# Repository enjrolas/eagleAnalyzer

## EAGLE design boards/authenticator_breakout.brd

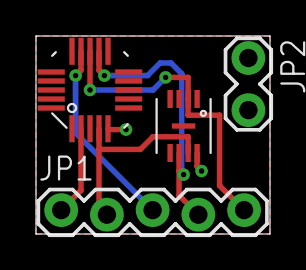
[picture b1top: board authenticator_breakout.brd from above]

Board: 2 copper layers, 13.0 x 11.0 mm, 4 parts (0 on the bottom side), 7 nets.

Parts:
JP1: 1X05_LOCK
JP2: 1X02_LOCK
U$2: AUTHENTICATORQFN; AUTH_QFN20
U$4: AUTHENTICATOR_2C; AUTH_SQC

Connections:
!AUTH_RESET: JP1.2, U$2.P$4, U$4.P$7
+3V3: JP2.2, U$2.P$5, U$4.P$8
GND: JP2.1, U$2.P$11, U$4.P$1
MODE0: JP1.3, U$2.P$14
MODE1: JP1.1, U$2.P$2
SCL: JP1.4, U$2.P$12, U$4.P$6
SDA: JP1.5, U$2.P$13, U$4.P$2

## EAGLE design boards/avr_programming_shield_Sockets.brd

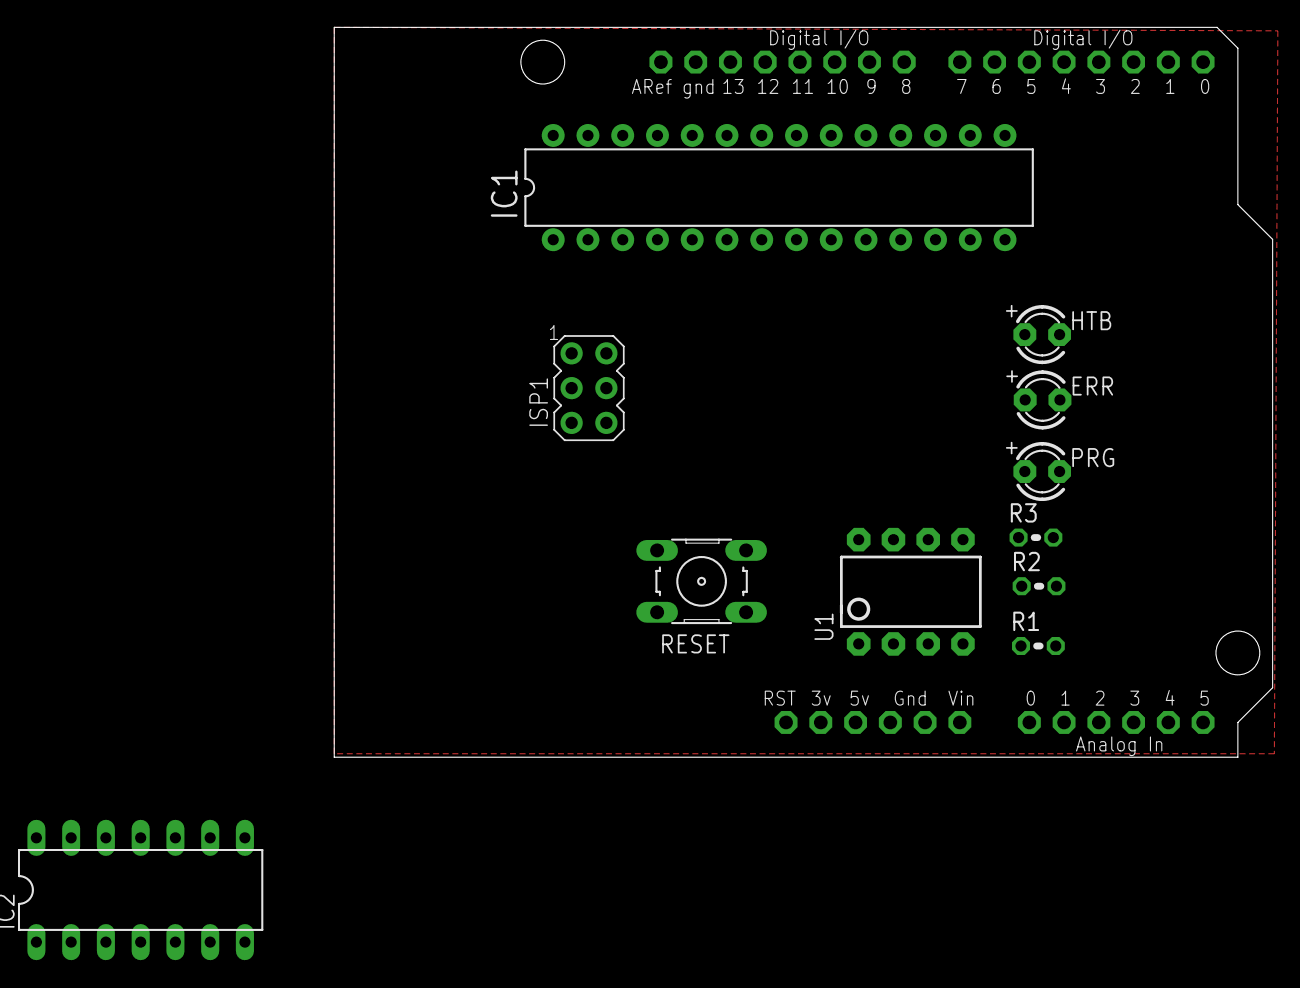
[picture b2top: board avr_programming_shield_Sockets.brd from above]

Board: 2 copper layers, 68.6 x 53.3 mm, 13 parts (0 on the bottom side), 13 nets, no tracks yet.

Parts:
E$1: OSHWLOGO_TOL_0.2
ERR: LED3MM
HTB: LED3MM
IC1: ATMEGA168PROUND; DIL28-3-ROUND
IC2: TINY24/44/84-PU; DIL14
ISP1: AVRISP-6; AVRISP
PRG: LED3MM
R1, R2, R3: 0204V
RESET: B3F-10XX
U1: TINY85-20-DIP; DIP08
U$1: ARDUINO-NOHOLE

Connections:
GND: IC1.8, IC1.22, IC2.14, ISP1.6, R1.1, R2.1, R3.1, RESET.1, RESET.2, U1.4, U$1.GND, U$1.GND1, U$1.GND2
unnamed: IC1.19, ISP1.3, U1.7, U$1.D13
unnamed: IC1.18, ISP1.1, U1.6, U$1.D12
unnamed: IC1.1, ISP1.5, U1.1, U$1.D10
unnamed: IC1.17, ISP1.4, U1.5, U$1.D11
unnamed: PRG.K, R1.2
unnamed: ERR.K, R2.2
unnamed: HTB.K, R3.2
unnamed: IC1.13, PRG.A
unnamed: ERR.A, IC1.14
unnamed: HTB.A, IC1.15
RESET: RESET.3, RESET.4, U$1.RESET
VCC: IC1.7, IC1.20, IC1.21, IC2.1, ISP1.2, U1.8, U$1.5V

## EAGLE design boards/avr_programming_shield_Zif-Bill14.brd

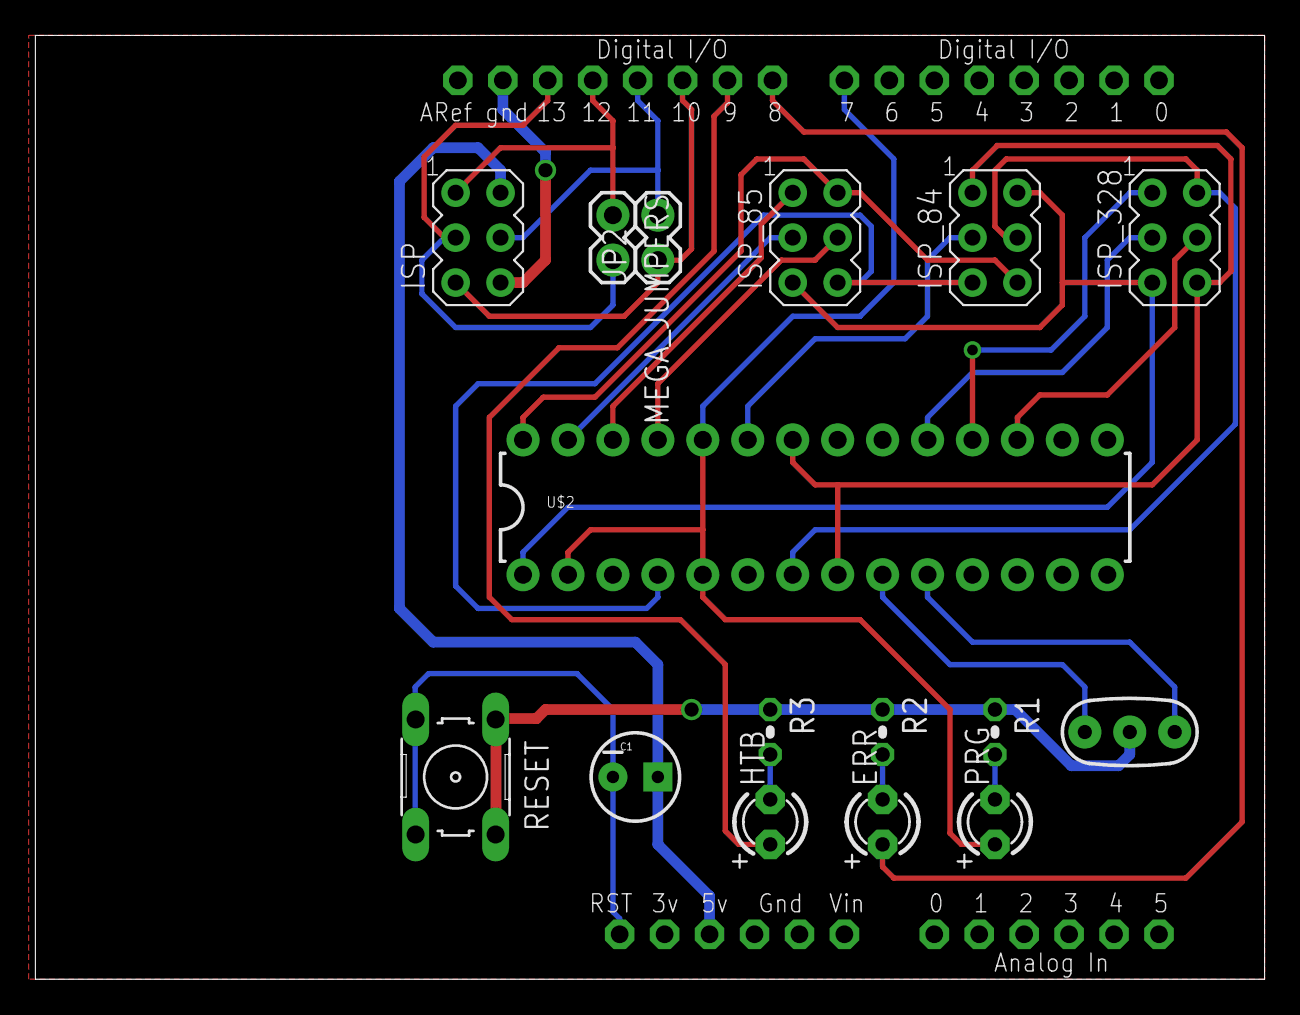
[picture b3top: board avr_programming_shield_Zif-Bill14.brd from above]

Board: 2 copper layers, 69.5 x 53.3 mm, 18 parts (0 on the bottom side), 27 nets.

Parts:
16MHZ: RESONATORPTH; RESONATOR-PTH
C1: 10uF; CPOL-RADIAL-10UF-25V
E$1: OSHWLOGO_TOL_0.2
ERR: LED3MM
HTB: LED3MM
ISP: AVRISP-6; AVRISP
ISP_84, ISP_85, ISP_328: AVRISP-6; AVRISP
JP2: 1X02
MEGA_JUMPERS: 1X02
PRG: LED3MM
R1, R2, R3: 0204V
RESET: B3F-10XX
U$1: ARDUINO-NOHOLE
U$2: ZIFSOCKET-28-3ZIFFSOCKET-28-3; DIL28-3-ZIF_SOCKET

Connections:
COMMON_D3: PRG.A, U$1.D7, U$2.2, U$2.5, U$2.24
GND: 16MHZ.2, ISP.6, R1.1, R2.1, R3.1, RESET.1, RESET.2, U$1.GND, U$1.GND1, U$1.GND2
unnamed: ISP_328.4, U$2.17
unnamed: ISP.3, MEGA_JUMPERS.2, U$1.D13
unnamed: ISP.1, MEGA_JUMPERS.1, U$1.D12
unnamed: ISP_328.1, U$2.18
unnamed: ISP.5, JP2.1, U$1.D10
unnamed: ISP_328.3, U$2.19
unnamed: PRG.K, R1.2
unnamed: ERR.K, R2.2
unnamed: HTB.K, R3.2
unnamed: ISP_84.4, ISP_328.2, U$2.7
unnamed: ISP.4, JP2.2, U$1.D11
unnamed: ISP_84.2, ISP_85.5, ISP_328.5, U$2.1
unnamed: ISP_84.3, U$2.23
unnamed: ISP_84.6, ISP_85.2, U$2.28
unnamed: HTB.A, U$1.D9
unnamed: ISP_84.5, ISP_85.6, U$2.4
unnamed: ISP_85.4, U$2.25
unnamed: ISP_85.1, U$2.26
unnamed: ISP_85.3, U$2.27
unnamed: 16MHZ.1, U$2.9
unnamed: ERR.A, U$1.D8
unnamed: 16MHZ.3, U$2.10
unnamed: ISP_84.1, ISP_328.6, U$2.8, U$2.22
RESET: C1.2, RESET.3, RESET.4, U$1.RESET
VCC: C1.1, ISP.2, U$1.5V

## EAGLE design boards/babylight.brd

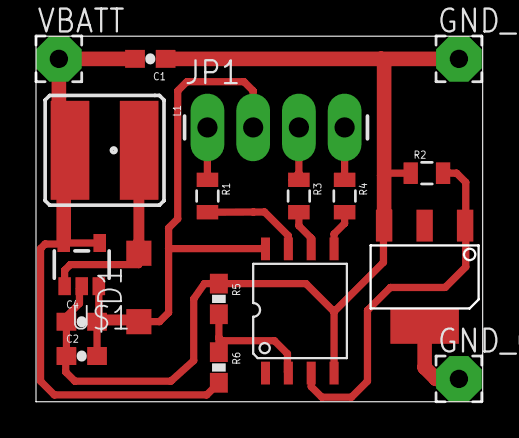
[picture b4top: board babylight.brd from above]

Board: 2 copper layers, 24.8 x 20.3 mm, 18 parts (0 on the bottom side), 13 nets.

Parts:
C1, C2: 22uF; 0603-CAP
C4: 1uF; 0603-CAP
D1: MBR0520; SOD123
GND_IN: 2,54/1,0
GND_OUT: 2,54/1,0
JP1: 1X04_LONGPADS
L1: 22uH; CR54
R1: 560; 0805
R2: 100K; 0805
R3, R4: 270; 0805
R5: 150K; 0603-RES
R6: 68K; 0603-RES
U$1: SP6641A; SOT23-5
U$2: ATTINY13; WSOIC-8
U$7: FQT13N06LTF; SOT-223
VBATT: 2,54/1,0

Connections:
5V: C2.2, C4.2, D1.C, JP1.2, U$1.3, U$2.8
BLU: JP1.4, R4.1
GND: C1.1, C2.1, C4.1, GND_IN.1, R2.1, R5.1, U$1.2, U$2.4, U$7.3
GND_OUT: GND_OUT.1, U$7.4
GRN: JP1.3, R3.1
unnamed: R5.2, R6.1, U$2.2
unnamed: D1.A, L1.P$1, U$1.1
unnamed: R4.2, U$2.5
unnamed: R3.2, U$2.6
unnamed: R1.2, U$2.7
RED: JP1.1, R1.1
SW: R2.2, U$2.3, U$7.1
VBATT: C1.2, L1.P$2, R6.2, U$1.4, U$1.5, VBATT.1

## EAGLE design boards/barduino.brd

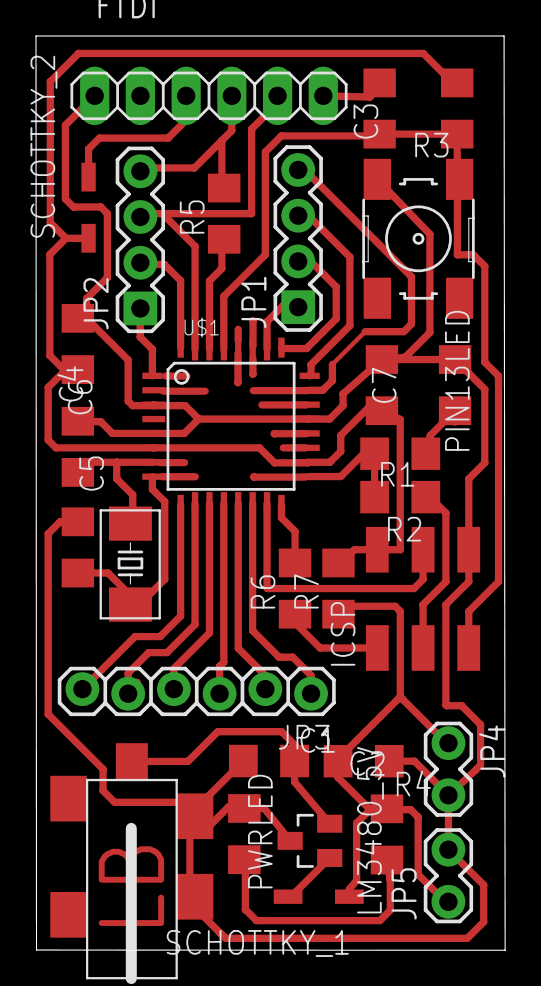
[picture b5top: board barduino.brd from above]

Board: 2 copper layers, 26.1 x 50.8 mm, 30 parts (0 on the bottom side), 28 nets.

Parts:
C1, C2: 10uF; 1206
C3, C6, C7: .1uF; 1206
C4, C5: 18pF; 1206
FTDI: 1X06
ICSP: 2X03SMD
J1: JACK.65MM; JACK_.65MM
JP1, JP2: 1X04
JP3: 1X06_LOCK
JP4, JP5: 1X02_LOCK
LM3480_5V: SOT23
PIN13LED: 1206
PWRLED: 1206
Q2: 16MHz; CS10
R1, R3, R4: 1K; 1206
R2, R5, R6, R7: 0; 1206
S1: 6MM_SWITCH
SCHOTTKY_1, SCHOTTKY_2: SOD123
U$1: ATMEGA88-THIN; TQFP32-08THIN

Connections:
A0: JP1.4, U$1.23
A1: JP1.3, U$1.24
A2: JP1.2, U$1.25
A3: JP1.1, U$1.26
CONNECT: FTDI.3, SCHOTTKY_2.ANODE
D0: FTDI.4, JP2.4, U$1.30
D1: FTDI.5, JP2.3, U$1.31
D2: JP2.2, U$1.32
D3: JP2.1, U$1.1
D5: JP3.6, U$1.9
D6: JP3.5, U$1.10
D7: JP3.4, U$1.11
D8: JP3.3, U$1.12
D9: JP3.2, U$1.13
D10: JP3.1, U$1.14
GND: C1.1, C2.1, C4.1, C5.1, C6.1, C7.1, FTDI.1, ICSP.6, J1.CONTACT, JP4.2, JP5.2, LM3480_5V.3, PIN13LED.2, PWRLED.2, S1.2, U$1.3, U$1.5, U$1.21
MISO-D12: ICSP.1, U$1.16
MOSI-D11: ICSP.4, U$1.15
unnamed: LM3480_5V.1, SCHOTTKY_1.ANODE
unnamed: PWRLED.1, R4.1
unnamed: C1.2, J1.PIN, LM3480_5V.2
unnamed: PIN13LED.1, R1.1
PB6: C4.2, Q2.P$2, U$1.7
PB7: C5.2, Q2.P$1, U$1.8
RESET: C3.1, ICSP.5, R3.1, S1.4, U$1.29
RTS#: C3.2, FTDI.6
SCK-D13: ICSP.3, R1.2, U$1.17
VCC: C2.2, C6.2, C7.2, ICSP.2, JP4.1, JP5.1, R3.2, R4.2, SCHOTTKY_1.CATHODE, SCHOTTKY_2.CATHODE, U$1.4, U$1.6, U$1.18

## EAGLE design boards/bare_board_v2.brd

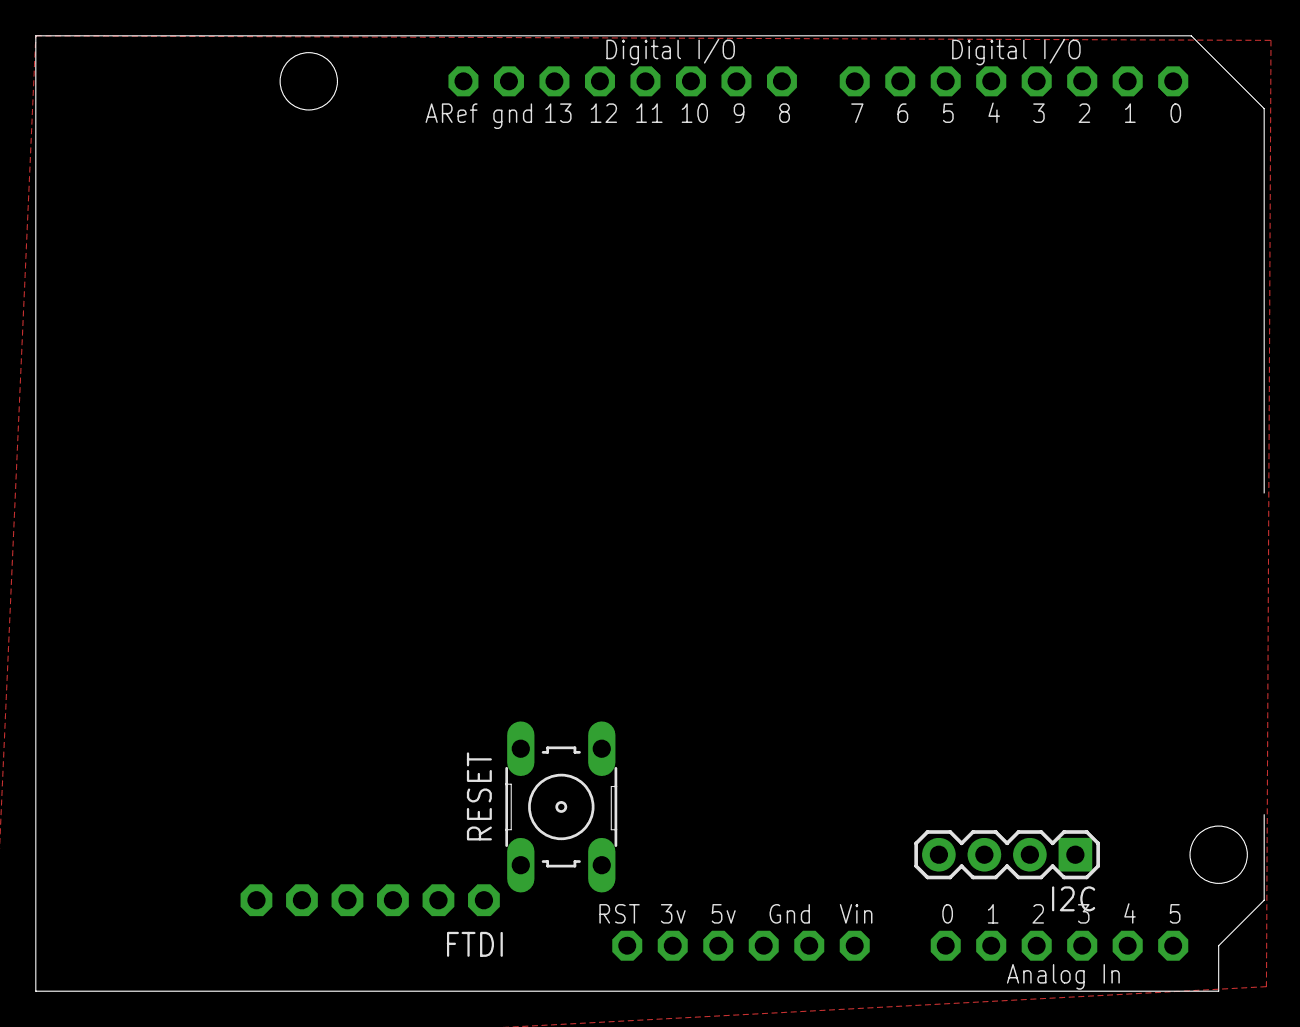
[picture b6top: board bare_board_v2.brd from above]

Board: 2 copper layers, 68.6 x 53.3 mm, 5 parts (0 on the bottom side), 5 nets, no tracks yet.

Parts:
E$1: OSHWLOGO_TOL_0.2
FTDI: FTDI; 1X06-CLEANBIG
I2C: 1X04
RESET: B3F-10XX
U$1: ARDUINO-NOHOLE

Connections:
GND: FTDI.6, I2C.2, RESET.1, RESET.2, U$1.GND, U$1.GND1, U$1.GND2
RESET: FTDI.1, RESET.3, RESET.4, U$1.RESET
SCL: I2C.4, U$1.A0
SDA: I2C.3, U$1.A1
VCC: FTDI.4, I2C.1, U$1.5V, U$1.AREF

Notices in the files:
parts and their libraries:
SparkFun-Connectors: Licensing: CC v3.0 Share-Alike You are welcome to use this library for commercial purposes.
